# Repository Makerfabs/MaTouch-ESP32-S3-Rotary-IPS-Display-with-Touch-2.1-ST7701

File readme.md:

MaTouch ESP32-S3 Rotary IPS Display with Touch 2.1 ST7701

```c++
/*
Version:		V1.0
Author:		Vincent
Create Date:	2023/8/24
Note:

    2023/8/29   V1.1    Change out factory test program

*/
```

# Makerfabs

[Makerfabs home page](https://www.makerfabs.com/)

[Makerfabs Wiki](https://wiki.makerfabs.com/)

## Intruduce

Product Link:

Wiki Link : 

## Features

Specs:
- Controller: ESP32-S3
- Wireless: WiFi& Bluetooth 5.0
- Touch Panel Driver: CST826
- USB: USB Native, Type-C
- Power Supply: USB Type-C 5.0V(4.0V~5.25V)
- Button: Flash button and reset button
- Arduino support: Yes
- MicroPython support: Yes
- Operation temperature: -40℃ to +85℃

# Usage

## Libraries

Related library versions

- Use type-c use cable connect USB-TTL to PC.
- Select "ESP32-S3 DEV Module"
- Select PSRAM "OPI PSRAM"

"mf_Lvgl" library is modified from Lvgl library (version 8.3.2). 

Please unzip "lib/mf_Lvgl.zip","TouchLib" and copy to arduino library directory.

## Example

### fw_test

Old factory test program.
Test screen display and touch, as well as ring encoders and press switches.

### fw_test_v2

Factory test program.
Test screen display and touch, as well as ring encoders and press switches. After press screen, it will change different screen.

### fs_test

No SD card is required, files are stored in SPIFFS in Flash, and the display is switched by rotary encoder.

Need use arduino-esp32fs-plugin upload picture. And install JPEGDEC version 1.2.8

[arduino-esp32fs-plugin](https://github.com/me-no-dev/arduino-esp32fs-plugin)

### stepper_control

Control stepper motor rotation speed, rotation direction.

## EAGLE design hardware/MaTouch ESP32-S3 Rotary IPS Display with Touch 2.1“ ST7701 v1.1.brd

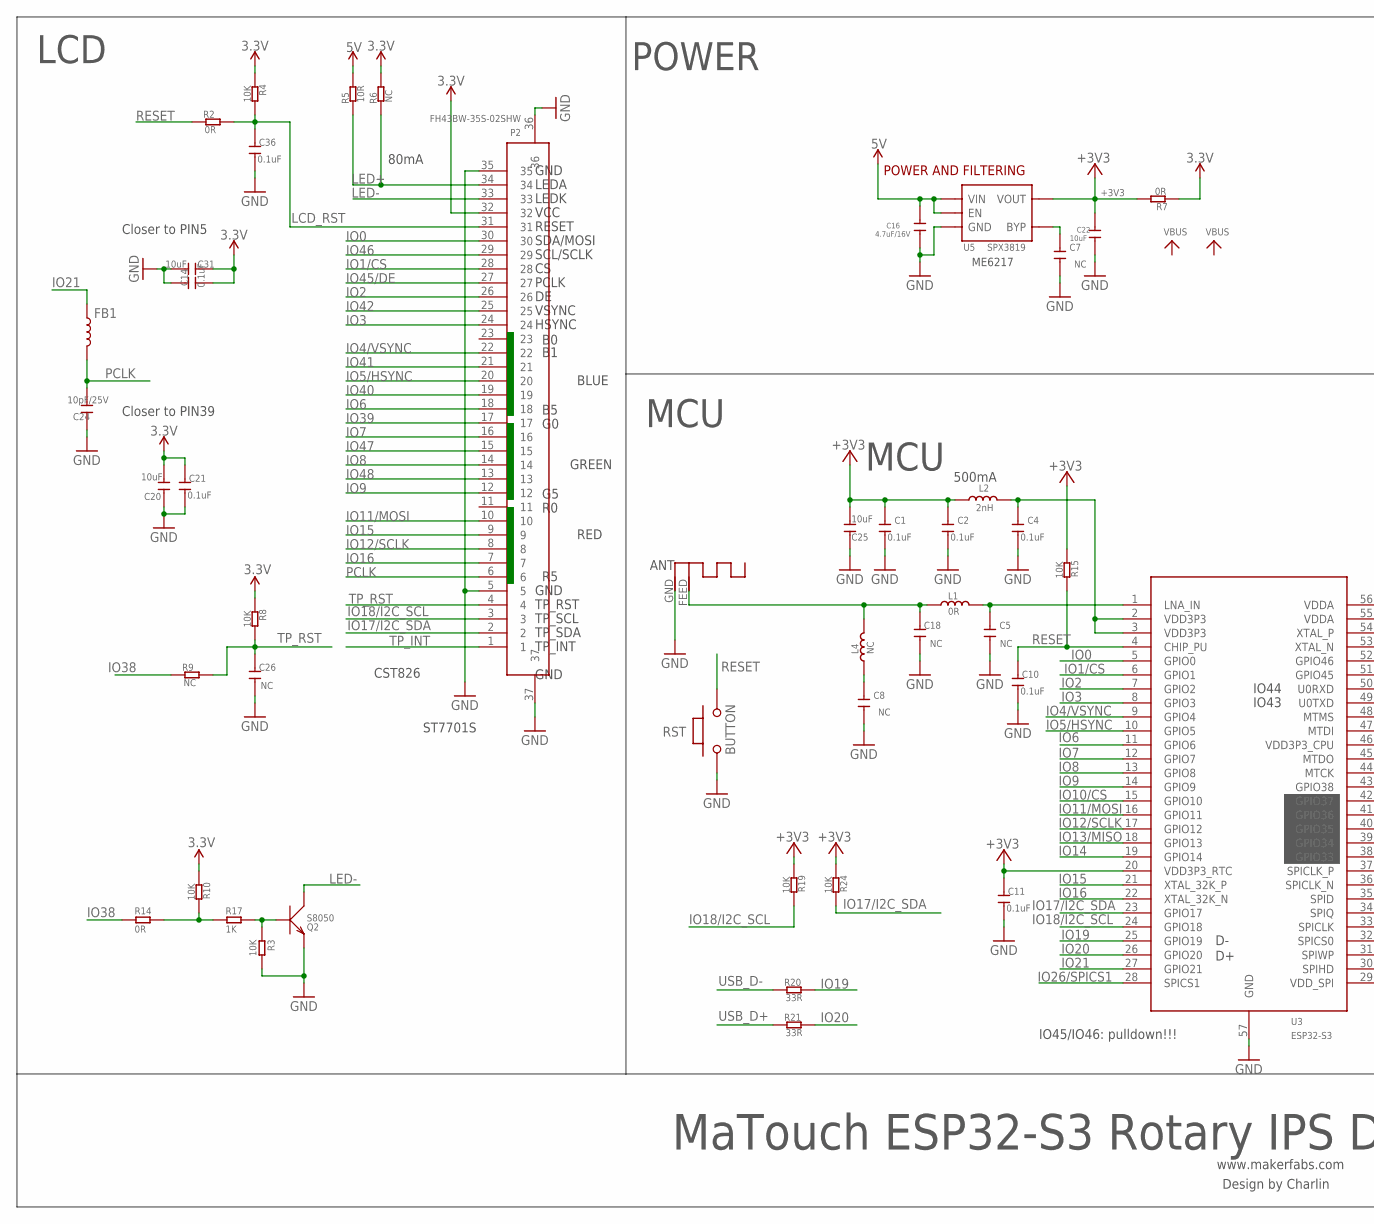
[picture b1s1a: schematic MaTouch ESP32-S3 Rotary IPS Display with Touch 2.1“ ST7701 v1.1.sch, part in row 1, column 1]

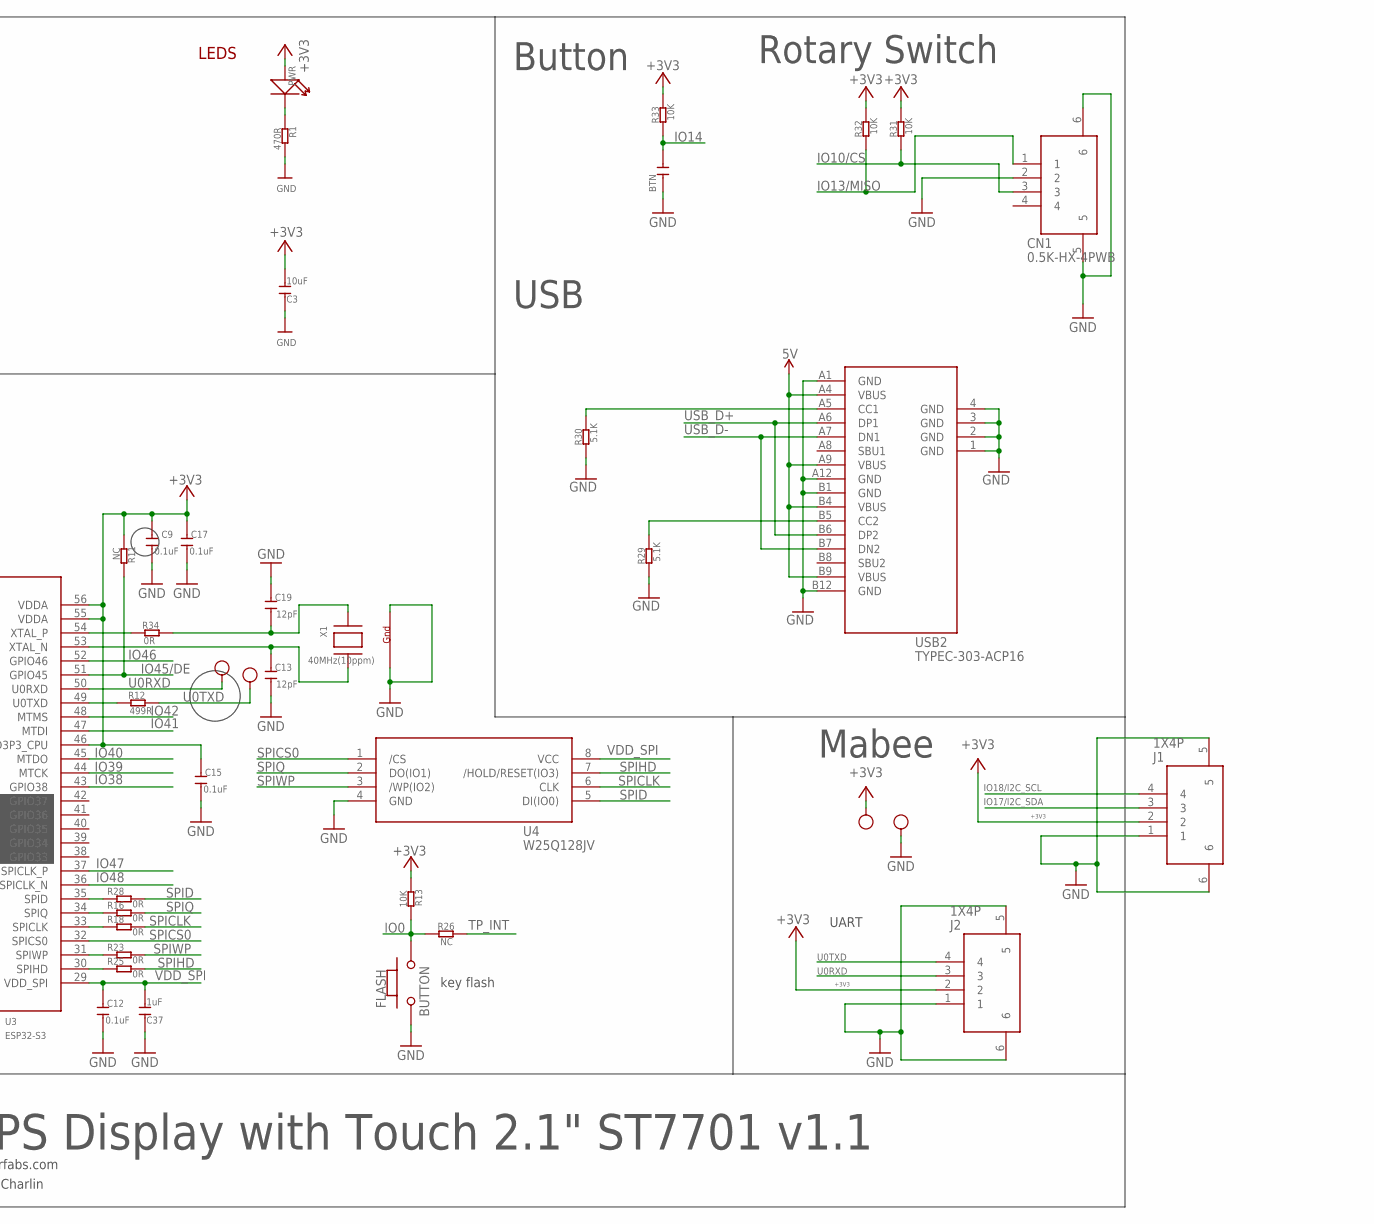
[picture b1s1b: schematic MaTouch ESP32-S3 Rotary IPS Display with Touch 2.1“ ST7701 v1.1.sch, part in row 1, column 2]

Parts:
3V3: TEST-POINT'4545'; TP-D45MIL; PARTNO DNP
ANT1: ANTENNA; RN-ANT
BTN: C'5.08'; CERAMIC-5.08
C1, C2, C4, C9, C10, C11, C12, C14, C15, C17, C21, C36: 0.1uF; DISCRETE_C0402
C3, C20, C25, C31: 10uF; DISCRETE_C0603
C5, C7, C8, C18, C26: NC; DISCRETE_C0402
C13, C19: 12pF; DISCRETE_C0402
C16: 4.7uF/16V; 0603
C22: 10uF; 0603
C24: 10pF/25V; DISCRETE_C0402
C37: 1uF; DISCRETE_C0603
CN1: 0.5K-HX-4PWB
FB1: INDUCTORFB-30OHM; 0603
FLASH: BUTTON; 157SW
GND: TEST-POINT'4545'; TP-D45MIL; PARTNO DNP
J1, J2: 1X4P; 1X4P-SMT1.25MM
L1: 0R; DISCRETE_L0402
L2: 2nH; DISCRETE_L0603
L4: NC; DISCRETE_L0402
P2: FH43BW-35S-02SHW; 1*35P-SMT0.4MM
PWR: DISCRETE_LED0603; DISCRETE_LED-0603
Q2: S8050; SOT23
R1: 470R; DISCRETE_R0402
R2, R7, R14, R16, R18, R23, R25, R28, R34: 0R; DISCRETE_R0402
R3, R4, R8, R10, R13, R15, R19, R24, R31, R32, R33: 10K; DISCRETE_R0402
R5: 10R; DISCRETE_R0402
R6, R9, R11, R26: NC; DISCRETE_R0402
R12: 499R; DISCRETE_R0402
R17: 1K; DISCRETE_R0402
R20, R21: 33R; DISCRETE_R0402
R29, R30: 5.1K; DISCRETE_R0402
RST: BUTTON; 157SW
RX: TEST-POINT'4545'; TP-D45MIL; PARTNO DNP
TX: TEST-POINT'4545'; TP-D45MIL; PARTNO DNP
U3: ESP32-S3; QFN56-7*7MM
U4: W25Q128JV; SOIC-8-208MIL
U5: SPX3819; SOT23-5
USB2: TYPEC-303-ACP16; TYPEC-303-SMD16
X1: 40MHz(10ppm); NX3225

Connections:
3.3V: C14.1, C20.2, C21.2, C31.1, P2.32, R4.2, R6.1, R7.2, R8.2, R10.2
5V: C16.1, R5.1, U5.1 (VIN), U5.3 (EN), USB2.A4 (VBUS), USB2.A9 (VBUS), USB2.B4 (VBUS), USB2.B9 (VBUS)
+3V3: 3V3.T, C1.2, C2.2, C3.2, C9.2, C11.2, C15.2, C17.2, C22.1, C25.2, J1.2, J2.2, L2.1, PWR.+, R7.1, R11.2, R13.2, R15.2, R19.2, R24.2, R31.1, R32.1, R33.1, U3.20 (VDD3P3_RTC), U3.46 (VDD3P3_CPU), U3.55 (VDDA), U3.56 (VDDA), U5.5 (VOUT)
GND: ANT1.GND, BTN.1, C1.1, C2.1, C3.1, C4.1, C5.1, C7.1, C8.1, C9.1, C10.1, C11.1, C12.1, C13.1, C14.2, C15.1, C16.2, C17.1, C18.1, C19.2, C20.1, C21.1, C22.2, C24.2, C25.1, C26.1, C31.2, C36.1, C37.1, CN1.2, CN1.5, CN1.6, FLASH.1, GND.T, J1.1, J1.5, J1.6, J2.1, J2.5, J2.6, P2.5, P2.35, P2.36, P2.37, Q2.2 (E), R1.1, R3.1, R29.2, R30.2, RST.1, U3.57 (GND), U4.4 (GND), U5.2 (GND), USB2.1 (GND), USB2.2 (GND), USB2.3 (GND), USB2.4 (GND), USB2.A1 (GND), USB2.A12 (GND), USB2.B1 (GND), USB2.B12 (GND), X1.2 (G2), X1.4 (G1)
IO0: FLASH.2, P2.30, R13.1, R26.2, U3.5 (GPIO0)
IO1/CS: P2.28, U3.6 (GPIO1)
IO2: P2.26, U3.7 (GPIO2)
IO3: P2.24, U3.8 (GPIO3)
IO4/VSYNC: P2.22, U3.9 (GPIO4)
IO5/HSYNC: P2.20, U3.10 (GPIO5)
IO6: P2.18, U3.11 (GPIO6)
IO7: P2.16, U3.12 (GPIO7)
IO8: P2.14, U3.13 (GPIO8)
IO9: P2.12, U3.14 (GPIO9)
IO10/CS: CN1.3, R31.2, U3.15 (GPIO10)
IO11/MOSI: P2.10, U3.16 (GPIO11)
IO12/SCLK: P2.8, U3.17 (GPIO12)
IO13/MISO: CN1.1, R32.2, U3.18 (GPIO13)
IO14: BTN.2, R33.2, U3.19 (GPIO14)
IO15: P2.9, U3.21 (XTAL_32K_P)
IO16: P2.7, U3.22 (XTAL_32K_N)
IO17/I2C_SDA: J1.3, P2.2, R24.1, U3.23 (GPIO17)
IO18/I2C_SCL: J1.4, P2.3, R19.1, U3.24 (GPIO18)
IO19: R20.1, U3.25 (GPIO19)
IO20: R21.1, U3.26 (GPIO20)
IO21: FB1.1, U3.27 (GPIO21)
IO26/SPICS1: U3.28 (SPICS1)
IO38: R9.2, R14.2, U3.43 (GPIO38)
IO39: P2.17, U3.44 (MTCK)
IO40: P2.19, U3.45 (MTDO)
IO41: P2.21, U3.47 (MTDI)
IO42: P2.25, U3.48 (MTMS)
IO45/DE: P2.27, R11.1, U3.51 (GPIO45)
IO46: P2.29, U3.52 (GPIO46)
IO47: P2.15, U3.37 (SPICLK_P)
IO48: P2.13, U3.36 (SPICLK_N)
LCD_RST: C36.2, P2.31, R2.1, R4.1
LED+: P2.34, R5.2, R6.2
LED-: P2.33, Q2.3 (C)
unnamed: ANT1.FEED, C18.2, L1.1, L4.2
unnamed: C5.2, L1.2, U3.1 (LNA_IN)
unnamed: R28.2, U3.35 (SPID)
unnamed: C8.2, L4.1
unnamed: R10.1, R14.1, R17.2
unnamed: PWR.-, R1.2
unnamed: Q2.1 (B), R3.2, R17.1
unnamed: R30.1, USB2.A5 (CC1)
unnamed: R29.1, USB2.B5 (CC2)
unnamed: C4.2, L2.2, U3.2 (VDD3P3), U3.3 (VDD3P3)
unnamed: R16.2, U3.34 (SPIQ)
unnamed: R34.2, U3.54 (XTAL_P)
unnamed: R18.2, U3.33 (SPICLK)
unnamed: R23.2, U3.31 (SPIWP)
unnamed: R25.2, U3.30 (SPIHD)
unnamed: R12.2, U3.49 (U0TXD)
unnamed: C13.2, U3.53 (XTAL_N), X1.3 (X2)
unnamed: C19.1, R34.1, X1.1 (X1)
unnamed: C7.2, U5.4 (BYP)
PCLK: C24.1, FB1.2, P2.6
RESET: C10.2, R2.2, R15.1, RST.2, U3.4 (CHIP_PU)
SPICLK: R18.1, U4.6 (CLK)
SPICS0: U3.32 (SPICS0), U4.1 (/CS)
SPID: R28.1, U4.5 (DI(IO0))
SPIHD: R25.1, U4.7 (/HOLD/RESET(IO3))
SPIQ: R16.1, U4.2 (DO(IO1))
SPIWP: R23.1, U4.3 (/WP(IO2))
TP_INT: P2.1, R26.1
TP_RST: C26.2, P2.4, R8.1, R9.1
U0RXD: J2.3, RX.T, U3.50 (U0RXD)
U0TXD: J2.4, R12.1, TX.T
USB_D+: R21.2, USB2.A6 (DP1), USB2.B6 (DP2)
USB_D-: R20.2, USB2.A7 (DN1), USB2.B7 (DN2)
VDD_SPI: C12.2, C37.2, U3.29 (VDD_SPI), U4.8 (VCC)

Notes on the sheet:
www.makerfabs.com
Design by Charlin
LEDS
POWER AND FILTERING
key flash
MaTouch ESP32-S3 Rotary IPS Display with Touch 2.1" ST7701 v1.1
POWER
CST826
Mabee
LCD
MCU
Closer to PIN5
LEDA
LEDK
VCC
TP_INT
RESET
SDA/MOSI
SCL/SCLK
PCLK
VSYNC
HSYNC
TP_SDA
TP_SCL
TP_RST
ST7701S
GND
BLUE
GREEN
RED
Closer to PIN39
ME6217
500mA
IO45/IO46: pulldown!!!
IO43
IO44
80mA
ANT
USB
Button

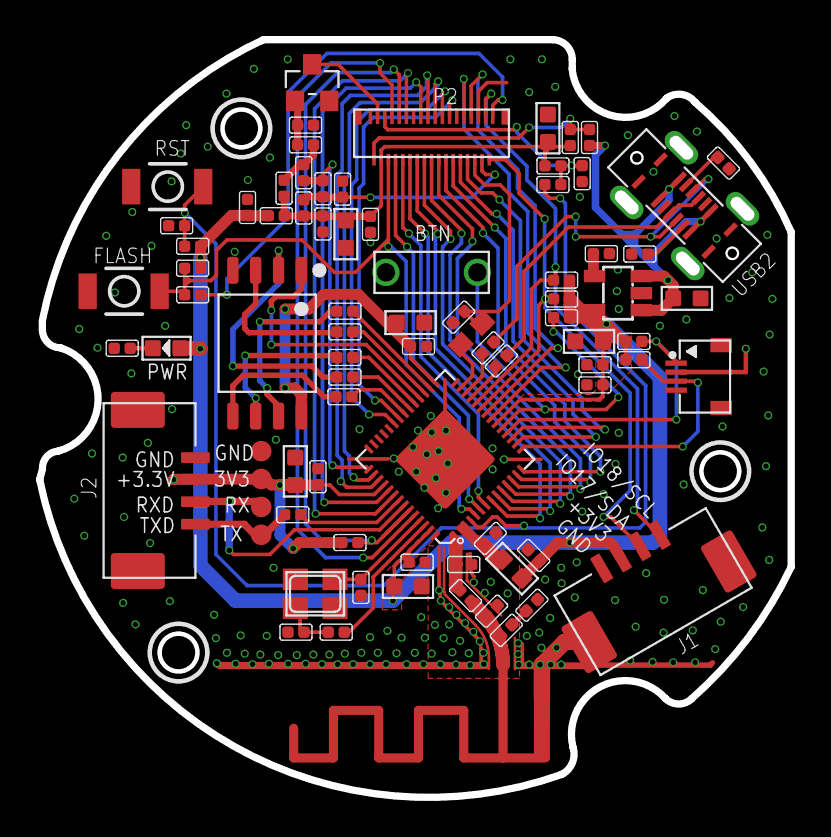
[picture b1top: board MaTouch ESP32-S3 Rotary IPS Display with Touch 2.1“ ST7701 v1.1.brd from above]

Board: 2 copper layers, 41.5 x 41.8 mm, 83 parts (1 on the bottom side), 72 nets.

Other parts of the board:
U$1: MAKERFABS_0.3

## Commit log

2023-08-17 Create
2023-08-22 Add demos
2023-08-24 Edit readme
2023-08-24 Add hardware
2023-08-29 Change firmware
2023-10-13 Add squareline demo
2023-10-18 Add schematic of PDF
2023-11-14 Add lvgl demo
2025-02-14 Add platformio demo

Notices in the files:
parts and their libraries:
SparkFun-Coils: Licensing: Creative Commons ShareAlike 4.0 International - https://creativecommons.org/licenses/by-sa/4.0
microbuilder: This work is placed in the public domain, and may be freely used for commercial and non-commercial work with the following conditions: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
